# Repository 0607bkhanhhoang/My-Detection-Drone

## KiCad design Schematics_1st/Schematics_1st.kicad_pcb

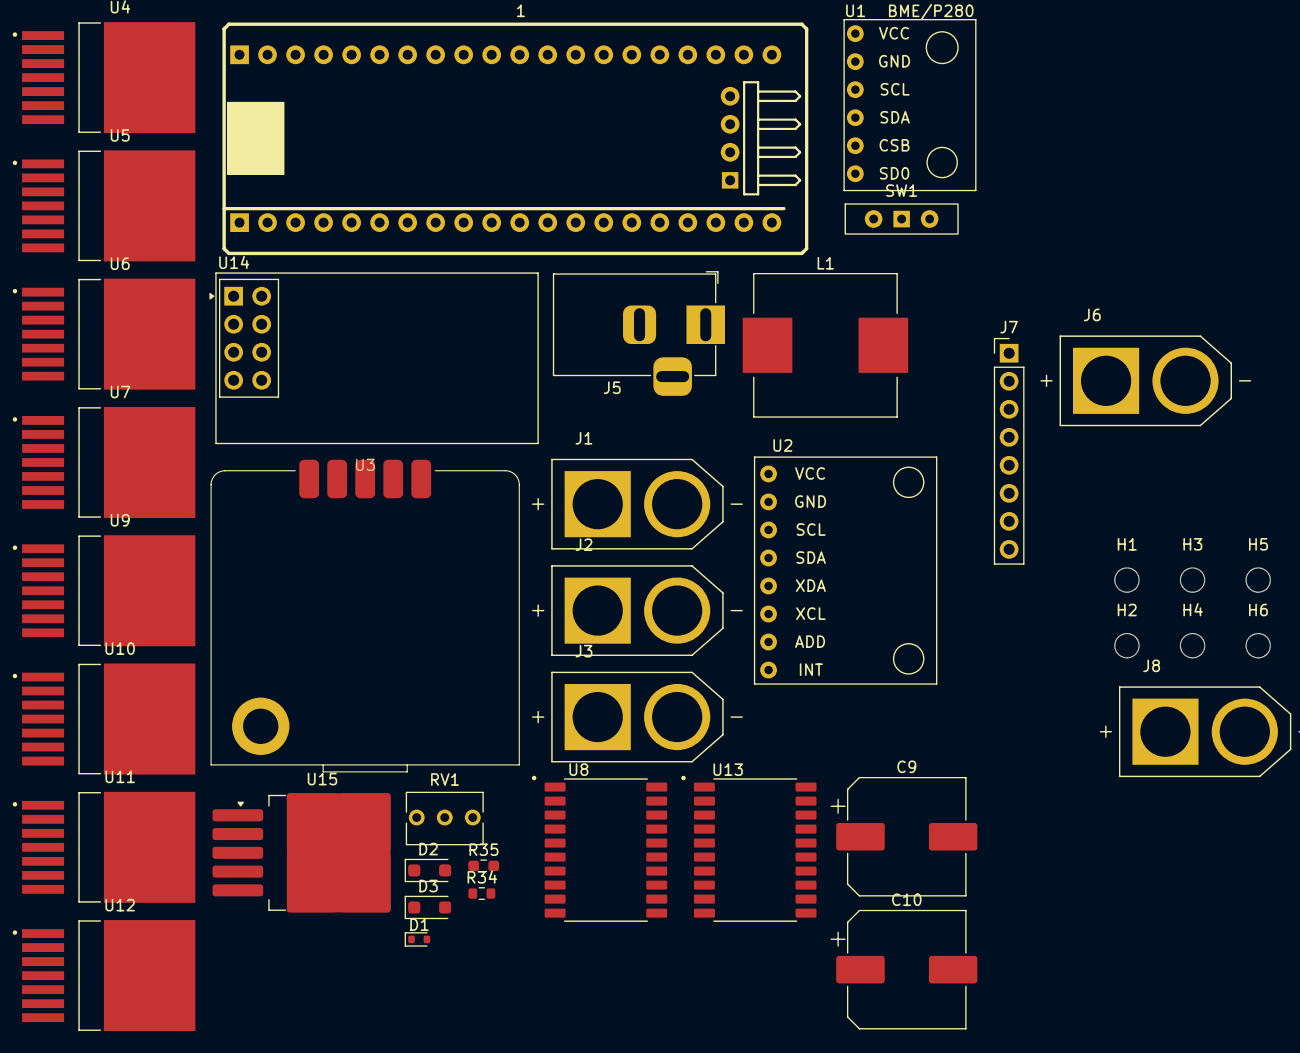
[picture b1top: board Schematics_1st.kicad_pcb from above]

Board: 2 copper layers, 41 parts (0 on the bottom side), 34 nets, no tracks yet.

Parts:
1: U4; STM32F4x1CxU6 WeActStudio
C9: 680u; CP_Elec_10x10.5
C10: 220u; CP_Elec_10x10.5
D1: 1N4148WT; D_SOD-523
D2, D3: BZT52Bxx; D_SOD-123F
H1, H2, H3, H4, H5, H6, H7, H8: MountingHole; MountingHole_2.2mm_M2
J1, J2, J3, J6, J8: XT60-M; AMASS_XT60-M
J5: Jack-DC; BarrelJack_Horizontal
J7: Conn_01x08_Pin; PinHeader_1x08_P2.54mm_Vertical
L1: 68u; L_Wuerth_HCI-1365
R34: 10k; R_0603_1608Metric
R35: 1k; R_0603_1608Metric_Pad0.98x0.95mm_HandSolder
RV1: 100k; Potentiometer_Bourns_3266Y_Vertical
SW1: SW_Wuerth_450301014042; SW_Slide-03_Wuerth-WS-SLTV_10x2.5x6.4_P2.54mm
U1: module_bme280
U2: module_mpu6050
U3: GT-U7; GT-U7_SMT
U4, U5, U6, U7, U9, U10, U11, U12: BTS7960B; DPAK127P1490X440-8N
U8, U13: 74HC244; SOIC127P1030X265-20N
U14: NRF24L01_Breakout; nRF24L01_Breakout
U15: LM2596S-ADJ; TO-263-5_TabPin3

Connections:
3.3V_VCC: 1.20 (3V3), U1.1 (VCC), U2.1 (VCC), U3.1 (VCC)
12V: C9.1, J5.1, U15.1 (VIN)
CSN: 1.30 (PA4), U14.4 (~CSN)
GND: 1.19 (GND), 1.39 (GND), C9.2, C10.2, D1.1 (K), D2.2 (A), D3.1 (K), J1.N (NEG), J2.N (NEG), J3.N (NEG), J5.2, J6.N (NEG), R34.2, RV1.2, U1.2 (GND), U2.2 (GND), U3.2 (GND), U4.1 (GND), U5.1 (GND), U6.1 (GND), U7.1 (GND), U8.1 (1OE), U8.3 (2Y0), U8.5 (2Y1), U8.7 (2Y2), U8.9 (2Y3), U8.10 (GND), U8.11 (2A3), U8.13 (2A2), U8.15 (2A1), U8.17 (2A0), U8.19 (2OE), U9.1 (GND), U10.1 (GND), U11.1 (GND), U12.1 (GND), U13.1 (1OE), U13.3 (2Y0), U13.5 (2Y1), U13.7 (2Y2), U13.9 (2Y3), U13.10 (GND), U13.11 (2A3), U13.13 (2A2), U13.15 (2A1), U13.17 (2A0), U13.19 (2OE), U14.1 (GND), U15.3 (GND), U15.5 (~ON/OFF)
MISO_NRF: 1.32 (PA6), U14.7 (MISO)
MOSI_NRF: 1.33 (PA7), U14.6 (MOSI)
unnamed: D2.1 (K), L1.1, U15.2 (OUT)
unnamed: D3.2 (A), R35.2
unnamed: R34.1, RV1.1, U15.4 (FB)
OUT1_NEGATIVE: 1.12 (PB4), J7.7
OUT1_POSITIVE: 1.5 (PA8), J7.8
OUT2_NEGATIVE: 1.13 (PB5), J7.5
OUT2_POSITIVE: 1.6 (PA9), J7.6
OUT3_NEGATIVE: 1.34 (PB0), J7.3
OUT3_POSITIVE: 1.7 (PA10), J7.4
OUT4_NEGATIVE: 1.35 (PB1), J7.1
OUT4_POSITIVE: 1.8 (PA11), J7.2
OUT_MOTOR1_N: U5.4 (OUT), U5.8 (OUT)
OUT_MOTOR1_P: U4.4 (OUT), U4.8 (OUT)
OUT_MOTOR2_N: U7.4 (OUT), U7.8 (OUT)
OUT_MOTOR2_P: U6.4 (OUT), U6.8 (OUT)
OUT_MOTOR3_N: U9.4 (OUT), U9.8 (OUT)
OUT_MOTOR3_P: U10.4 (OUT), U10.8 (OUT)
OUT_MOTOR4_N: U11.4 (OUT), U11.8 (OUT)
OUT_MOTOR4_P: U12.4 (OUT), U12.8 (OUT)
SCK: 1.31 (PA5), U14.5 (SCK)
SCL_6050: 1.37 (PB10), U2.3 (SCL)
SCL_BME280: 1.14 (PB6), U1.3 (SCL)
SDA_6050: 1.11 (PB3), U2.4 (SDA)
SDA_BME280: 1.15 (PB7), U1.4 (SDA)
VCC_5V: U8.20 (VCC), U13.20 (VCC), U14.2 (VCC)
VSOURCE: J1.P (POS), J2.P (POS), J3.P (POS), J8.P (POS), SW1.3 (A)
VSource_5V: C10.1, L1.2, R35.1, RV1.3
V_SOURCE: SW1.1 (B), U4.7 (VS), U5.7 (VS), U6.7 (VS), U7.7 (VS), U9.7 (VS), U10.7 (VS), U11.7 (VS), U12.7 (VS)

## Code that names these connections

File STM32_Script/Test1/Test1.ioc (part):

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Mcu.Name=STM32F401C(B-C)Ux
Mcu.Package=UFQFPN48
Mcu.UserName=STM32F401CCUx
PA10.GPIOParameters=GPIO_Label
PA10.GPIO_Label=MOTOR_3_P
PA10.Signal=S_TIM1_CH3
PA11.GPIOParameters=GPIO_Label
PA11.GPIO_Label=MOTOR_4_P
PA11.Signal=S_TIM1_CH4
PA13.Mode=Serial_Wire
PA13.Signal=SYS_JTMS-SWDIO
PA14.Mode=Serial_Wire
PA14.Signal=SYS_JTCK-SWCLK
PA2.Mode=Asynchronous
PA2.Signal=USART2_TX
PA3.Mode=Asynchronous
PA3.Signal=USART2_RX
PA4.Mode=NSS_Signal_Hard_Input
PA4.Signal=SPI1_NSS
PA5.Mode=Full_Duplex_Master
PA5.Signal=SPI1_SCK
PA6.Mode=Full_Duplex_Master
PA6.Signal=SPI1_MISO
PA7.Mode=Full_Duplex_Master
PA7.Signal=SPI1_MOSI
PA8.GPIOParameters=GPIO_Label
PA8.GPIO_Label=MOTOR_1_P
PA8.Signal=S_TIM1_CH1
PA9.GPIOParameters=GPIO_Label
PA9.GPIO_Label=MOTOR_2_P
PA9.Signal=S_TIM1_CH2
PB0.GPIOParameters=GPIO_Label
PB0.GPIO_Label=MOTOR_3_N
PB0.Signal=S_TIM3_CH3
PB1.GPIOParameters=GPIO_Label
PB1.GPIO_Label=MOTOR_4_N
PB1.Signal=S_TIM3_CH4
PB10.Mode=I2C
PB10.Signal=I2C2_SCL
PB3.Mode=I2C
PB3.Signal=I2C2_SDA
PB4.GPIOParameters=GPIO_Label
PB4.GPIO_Label=MOTOR_1_N
PB4.Signal=S_TIM3_CH1
PB5.GPIOParameters=GPIO_Label
PB5.GPIO_Label=MOTOR_2_N
PB5.Signal=S_TIM3_CH2
PB6.Mode=I2C
PB6.Signal=I2C1_SCL
PB7.Mode=I2C
PB7.Signal=I2C1_SDA
PC14-OSC32_IN.Mode=LSE-External-Oscillator
PC14-OSC32_IN.Signal=RCC_OSC32_IN
PC15-OSC32_OUT.Mode=LSE-External-Oscillator
PC15-OSC32_OUT.Signal=RCC_OSC32_OUT
PH0\ -\ OSC_IN.Mode=HSE-External-Oscillator
PH0\ -\ OSC_IN.Signal=RCC_OSC_IN
PH1\ -\ OSC_OUT.Mode=HSE-External-Oscillator
PH1\ -\ OSC_OUT.Signal=RCC_OSC_OUT
RCC.HSE_VALUE=25000000
RCC.SYSCLKFreq_VALUE=72000000
RCC.SYSCLKSource=RCC_SYSCLKSOURCE_PLLCLK
board=custom

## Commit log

2024-12-30 KhanhHoang added his PCB
